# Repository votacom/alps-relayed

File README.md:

# alps-relayed
Input selection circuit board replacing the Alps ASD-1025 and ASD-1017 motor switches (and possibly others) in Pioneer's A-50xR, A-550R and A-450R amplifiers (and possibly others), using fast relays. The switching circuit supports the amplifier's native remote control and is faster than the motor switch (typically 42 milliseconds on average).

## Supported amplifiers
This circuit board is designed to replace ASD-1025 in the Pioneer A-502R, A-502R-G, A-503R, and A-503R-G amplifier models. It can also replace ASD-1017 in the Pioneer A-501R, A-550R and A-450R models, though with the downside of the "Source" recording input selection not working anymore (unless four jumpers are added, but then tape looping becomes possible, which is inhibited by ASD-1017). Since the ASD-1025 was also used in A-602R, it may be possible to use it in this model as well, but this has not been verified.

## Versions
There are two versions of the replacement board: v1 and v2.
v1 is larger, connects to the motor pin holes via individual connectors, and includes a direct plug connector to the motor driver IC pin holes and an additional stabilizing blind plug connector. Its layout is only applicable to the A-502R and A-503R models.
v2 is more compact, uses only three broad connectors to the motor pin holes, and does not directly plug into the motor driver IC pin holes, but uses a patch wire connector instead. This way, it can also be used in the A-501R, A-550R and A-450R models.
The two versions also slightly differ in their circuitry.

## Installation in Pioneer A-502R / A-503R

### v1 Installation
To install the v1 replacement board,
1. uninstall (unsolder) from the amplifier's input assembly board
   - the switch motor,
   - the motor driver IC (TA7291S), and
   - the nearby tall electrolytic capacitor (labelled C293),
2. solder simple vertical pin headers (e.g. Samtek TSW-1xx) into the input assembly board as follows:
   - a single-row 9-pin header strip where the motor driver IC was,
   - a single pin in each of the now-free motor's drill holes that would be connected by the replacement board (20 in total), and
   - a single pin in the free drill hole that would be connected by the replacement board's single corner socket, right next to the ribbon cable socket,
3. plug the replacement board on the input assembly board, aligning the selection board's new pins with the replacement board's sockets.

### v2 Installation
To install the v2 replacement board,
1. uninstall (unsolder) from the amplifier's input assembly board
   - the switch motor, and
   - the motor driver IC (TA7291S),
2. solder a single-row 9-pin header strip (e.g. Samtek TSW-1xx) to replace the motor driver IC,
3. from three Hirose DF3A-12P-2DSA pin headers, clip off every other pin (the odd-numbered pins) and solder them into the upper rows of the three double-row motor drill holes (pay attention to orientation),
4. stick a plain pin (min. 7mm) in each of the replacement board's two "Selection" sockets,
5. plug the replacement board on the input assembly board (the two plain pins extending from the replacement board should go through pin holes the on input assembly board),
6. use four individual jumper wires to connect the replacement board's +5V, GND, ↑, and ↓ pins to four of the motor driver IC's replacement header strip's pins (counted from left to right, starting at 1) as follows:
   - +5V connects to pin number 4,
   - GND connects to pin number 5,
   - ↑ and ↓ connect to pins number 1 and 9 in any order.

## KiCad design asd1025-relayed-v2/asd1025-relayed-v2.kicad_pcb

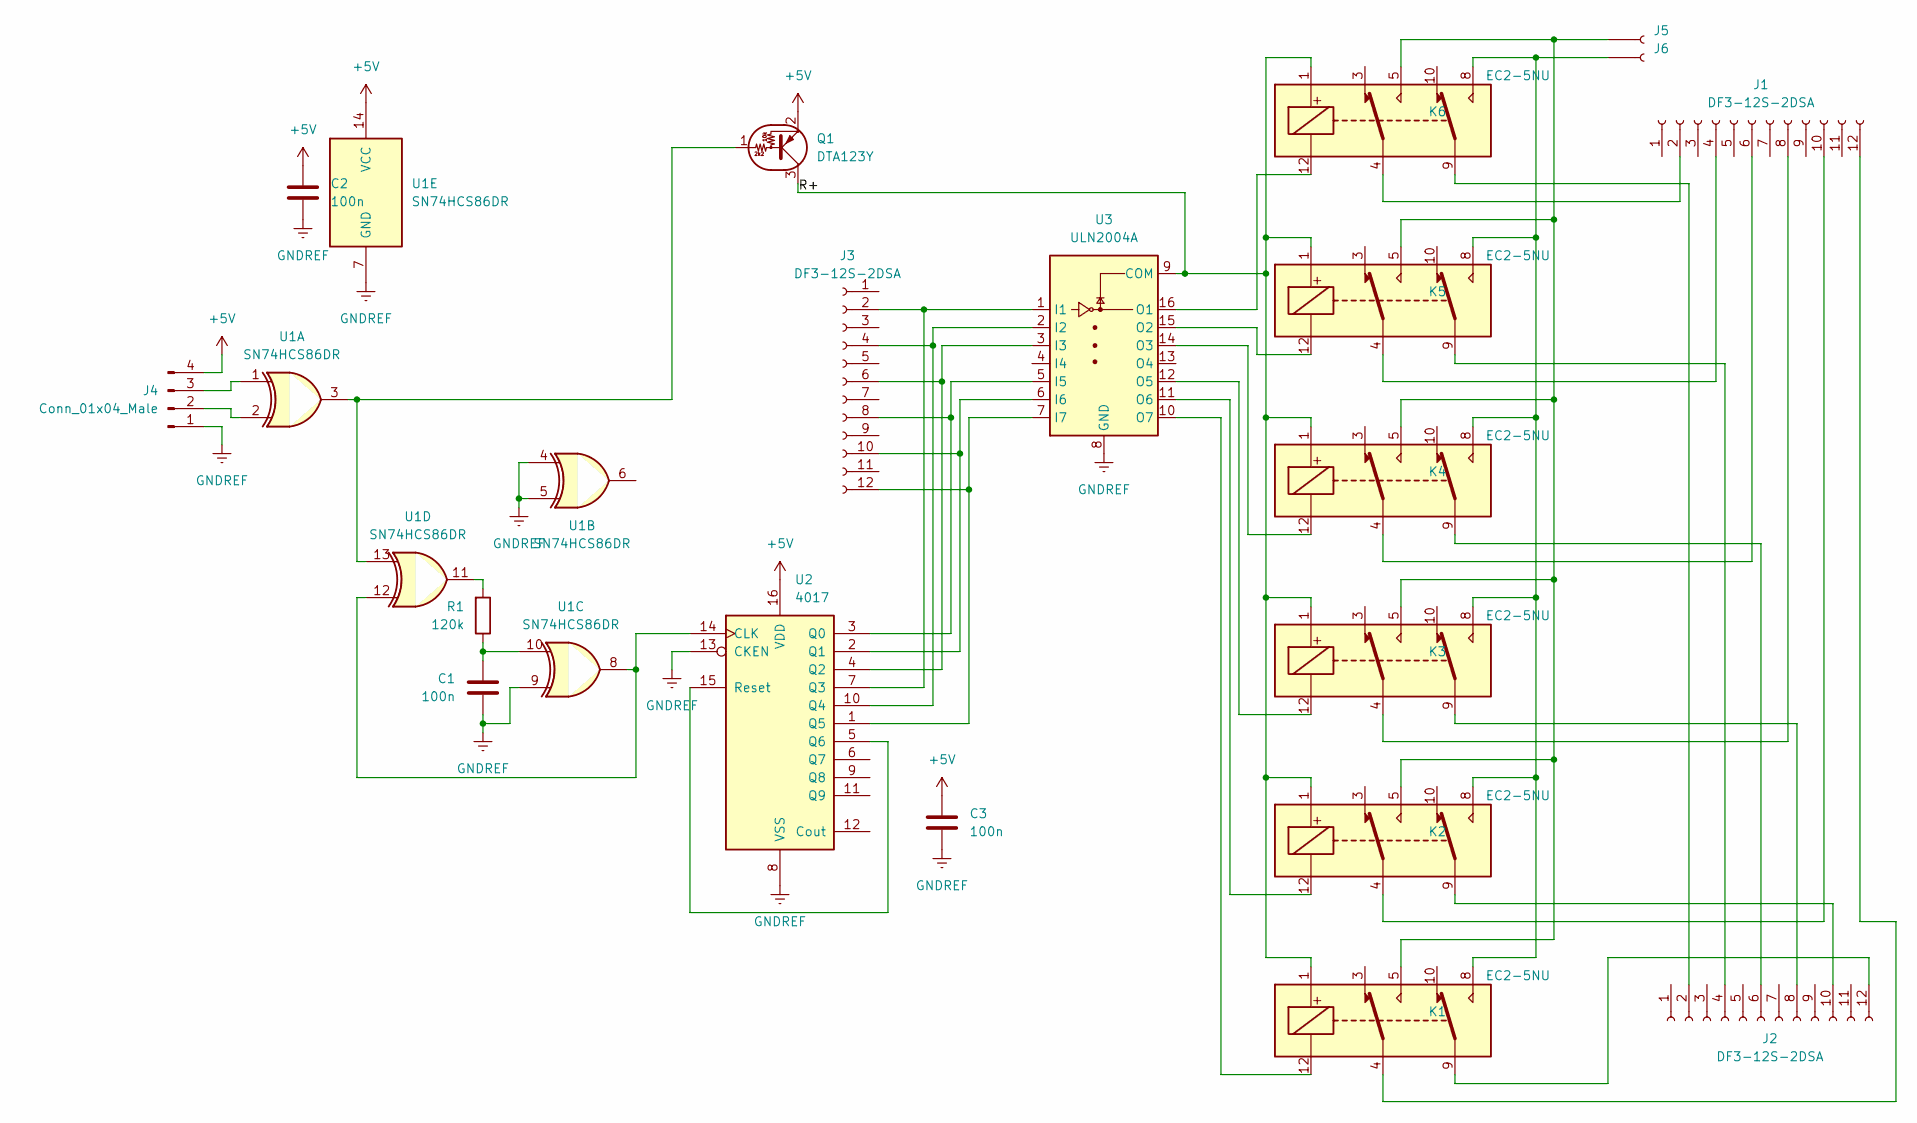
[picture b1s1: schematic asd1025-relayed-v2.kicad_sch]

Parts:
C1, C3: 100n; C_Disc_D5.1mm_W3.2mm_P5.00mm
C2: 100n; C_0402_1005Metric_Pad0.74x0.62mm_HandSolder
J1, J2, J3: DF3-12S-2DSA; Hirose_DF3-12S-2DSA_1x12_P2.00mm_Vertical
J4: Conn_01x04_Male; PinHeader_1x04_P2.54mm_Horizontal
J5, J6: Conn_01x01_Female; PinSocket_1x01_P2.54mm_Vertical
K1, K2, K3, K4, K5, K6: EC2-5NU; Relay_DPDT_Kemet_EC2
Q1: DTA123Y; SOT-23
R1: 120k; R_Axial_DIN0207_L6.3mm_D2.5mm_P10.16mm_Horizontal
U1: SN74HCS86DR; SOIC-14_3.9x8.7mm_P1.27mm
U2: 4017; SOIC-16_3.9x9.9mm_P1.27mm
U3: ULN2004A; DIP-16_W7.62mm

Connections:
+5V: C2.1, C3.1, J4.4, Q1.2 (E), U1.14 (VCC), U2.16 (VDD)
/R+: K1.1, K2.1, K3.1, K4.1, K5.1, K6.1, Q1.3 (C), U3.9 (COM)
GNDREF: C1.1, C2.2, C3.2, J4.1, U1.4, U1.5, U1.7 (GND), U1.9, U2.8 (VSS), U2.13 (CKEN), U3.8 (GND)
unnamed: C1.2, R1.1, U1.10
unnamed: J1.2, K6.4
unnamed: J1.4, K5.4
unnamed: J1.6, K4.4
unnamed: J1.8, K3.4
unnamed: J1.10, K2.4
unnamed: J1.12, K1.4
unnamed: J2.2, K6.9
unnamed: J2.4, K5.9
unnamed: J2.6, K4.9
unnamed: J2.8, K3.9
unnamed: J2.10, K2.9
unnamed: J2.12, K1.9
unnamed: J3.2, U2.7 (Q3), U3.1 (I1)
unnamed: J3.4, U2.10 (Q4), U3.2 (I2)
unnamed: J3.6, U2.4 (Q2), U3.3 (I3)
unnamed: J3.8, U2.3 (Q0), U3.5 (I5)
unnamed: J3.10, U2.2 (Q1), U3.6 (I6)
unnamed: J3.12, U2.1 (Q5), U3.7 (I7)
unnamed: J4.2, U1.2
unnamed: J4.3, U1.1
unnamed: J5.1, K1.5, K2.5, K3.5, K4.5, K5.5, K6.5
unnamed: J6.1, K1.8, K2.8, K3.8, K4.8, K5.8, K6.8
unnamed: K1.12, U3.10 (O7)
unnamed: K2.12, U3.11 (O6)
unnamed: K3.12, U3.12 (O5)
unnamed: K4.12, U3.14 (O3)
unnamed: K5.12, U3.15 (O2)
unnamed: K6.12, U3.16 (O1)
unnamed: R1.2, U1.11
unnamed: Q1.1 (B), U1.3, U1.13
unnamed: U1.8, U1.12, U2.14 (CLK)
unnamed: U2.5 (Q6), U2.15 (Reset)

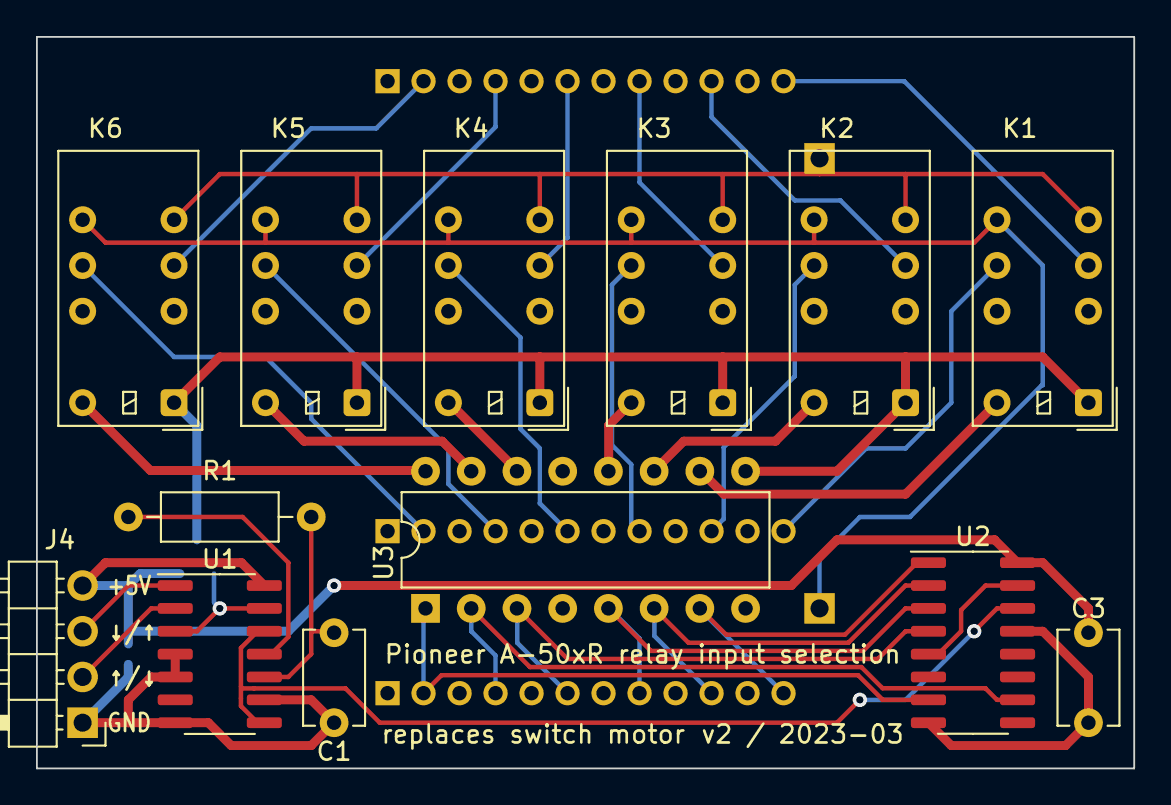
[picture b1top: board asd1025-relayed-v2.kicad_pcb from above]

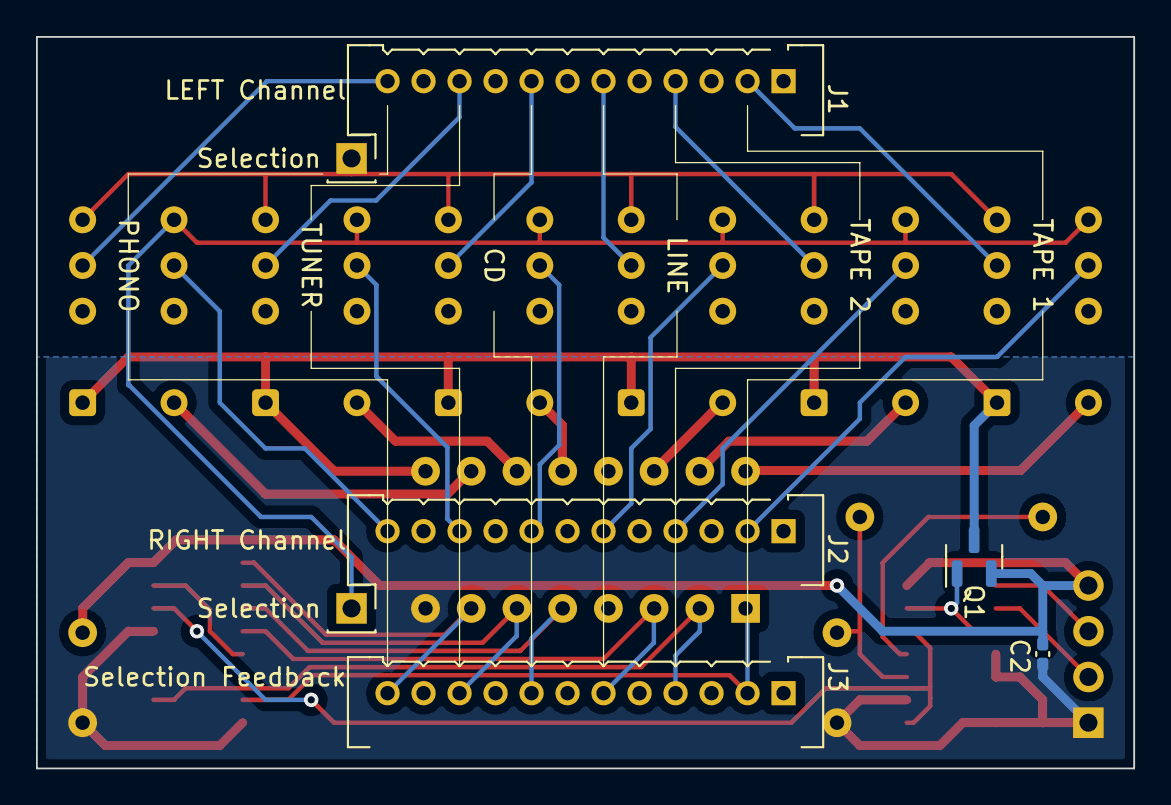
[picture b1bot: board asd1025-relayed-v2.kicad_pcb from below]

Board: 2 copper layers, 61.0 x 40.6 mm, 20 parts (7 on the bottom side), 36 nets.

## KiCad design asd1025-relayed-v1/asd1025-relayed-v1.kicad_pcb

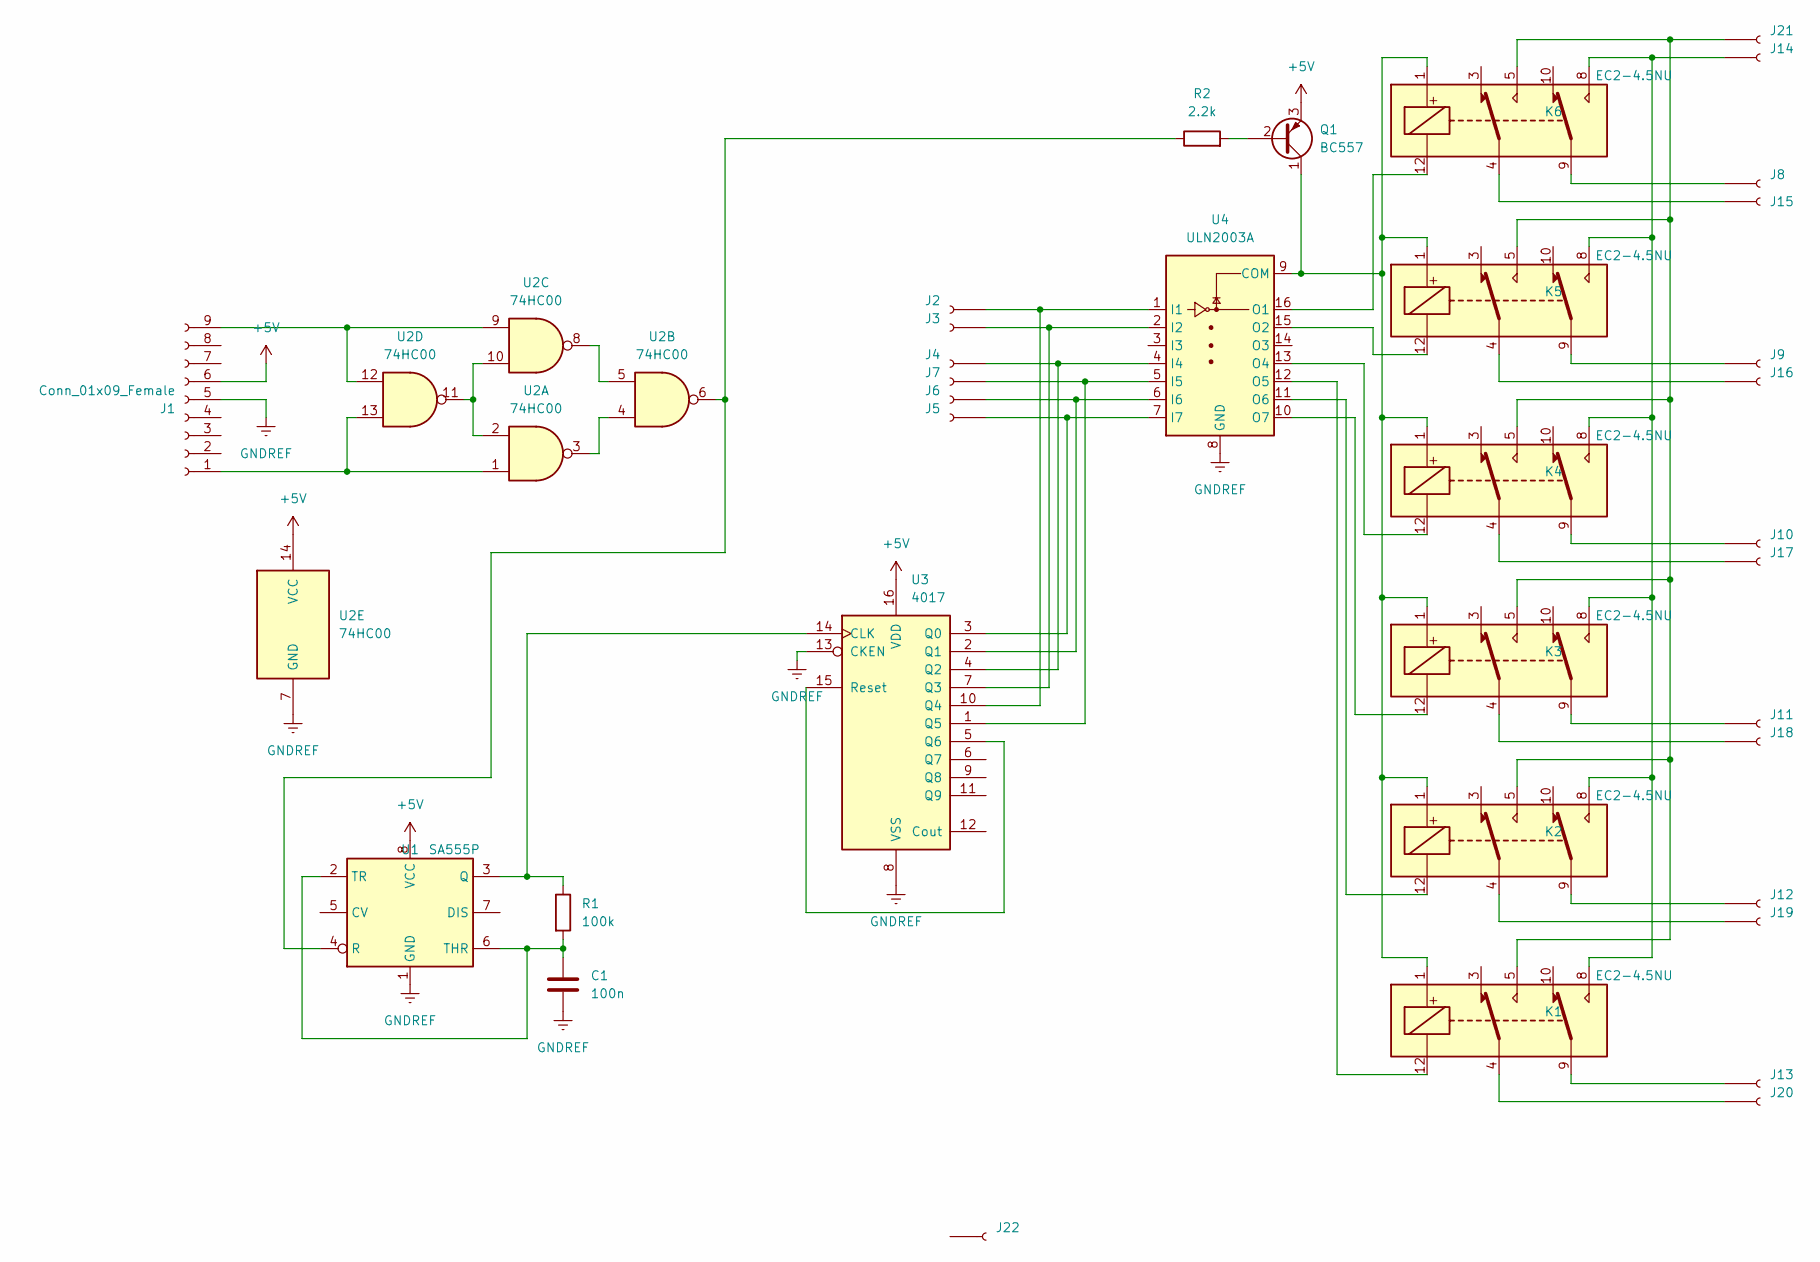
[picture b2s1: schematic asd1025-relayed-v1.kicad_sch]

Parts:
C1: 100n; C_Disc_D5.1mm_W3.2mm_P5.00mm
J1: Conn_01x09_Female; PinSocket_1x09_P2.54mm_Vertical
J2, J3, J4, J5, J6, J7, J8, J9, J10, J11, J12, J13, J14, J15, J16, J17, J18, J19, J20, J21, J22: Conn_01x01_Female; PinSocket_1x01_P2.54mm_Vertical
K1, K2, K3, K4, K5, K6: EC2-4.5NU; Relay_DPDT_Kemet_EC2
Q1: BC557; TO-92_Inline_Wide
R1: 100k; R_Axial_DIN0207_L6.3mm_D2.5mm_P10.16mm_Horizontal
R2: 2.2k; R_Axial_DIN0207_L6.3mm_D2.5mm_P10.16mm_Horizontal
U1: SA555P; DIP-8_W7.62mm
U2: 74HC00; DIP-14_W7.62mm
U3: 4017; DIP-16_W7.62mm
U4: ULN2003A; DIP-16_W7.62mm

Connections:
+5V: J1.6, Q1.3 (E), U1.8 (VCC), U2.14 (VCC), U3.16 (VDD)
GNDREF: C1.2, J1.5, U1.1 (GND), U2.7 (GND), U3.8 (VSS), U3.13 (CKEN), U4.8 (GND)
unnamed: C1.1, R1.2, U1.2 (TR), U1.6 (THR)
unnamed: J1.1, U2.1, U2.13
unnamed: J2.1, U3.10 (Q4), U4.1 (I1)
unnamed: J3.1, U3.7 (Q3), U4.2 (I2)
unnamed: J4.1, U3.4 (Q2), U4.4 (I4)
unnamed: J5.1, U3.3 (Q0), U4.7 (I7)
unnamed: J6.1, U3.2 (Q1), U4.6 (I6)
unnamed: J7.1, U3.1 (Q5), U4.5 (I5)
unnamed: J8.1, K6.9
unnamed: J9.1, K5.9
unnamed: J10.1, K4.9
unnamed: J11.1, K3.9
unnamed: J12.1, K2.9
unnamed: J13.1, K1.9
unnamed: J14.1, K1.8, K2.8, K3.8, K4.8, K5.8, K6.8
unnamed: J15.1, K6.4
unnamed: J16.1, K5.4
unnamed: J17.1, K4.4
unnamed: J18.1, K3.4
unnamed: J19.1, K2.4
unnamed: J20.1, K1.4
unnamed: J21.1, K1.5, K2.5, K3.5, K4.5, K5.5, K6.5
unnamed: K1.1, K2.1, K3.1, K4.1, K5.1, K6.1, Q1.1 (C), U4.9 (COM)
unnamed: K1.12, U4.12 (O5)
unnamed: K2.12, U4.11 (O6)
unnamed: K3.12, U4.10 (O7)
unnamed: K4.12, U4.13 (O4)
unnamed: K5.12, U4.15 (O2)
unnamed: K6.12, U4.16 (O1)
unnamed: Q1.2 (B), R2.2
unnamed: R1.1, U1.3 (Q), U3.14 (CLK)
unnamed: R2.1, U1.4 (R), U2.6
unnamed: U2.3, U2.4
unnamed: U2.5, U2.8
unnamed: J1.9, U2.9, U2.12
unnamed: U2.2, U2.10, U2.11
unnamed: U3.5 (Q6), U3.15 (Reset)

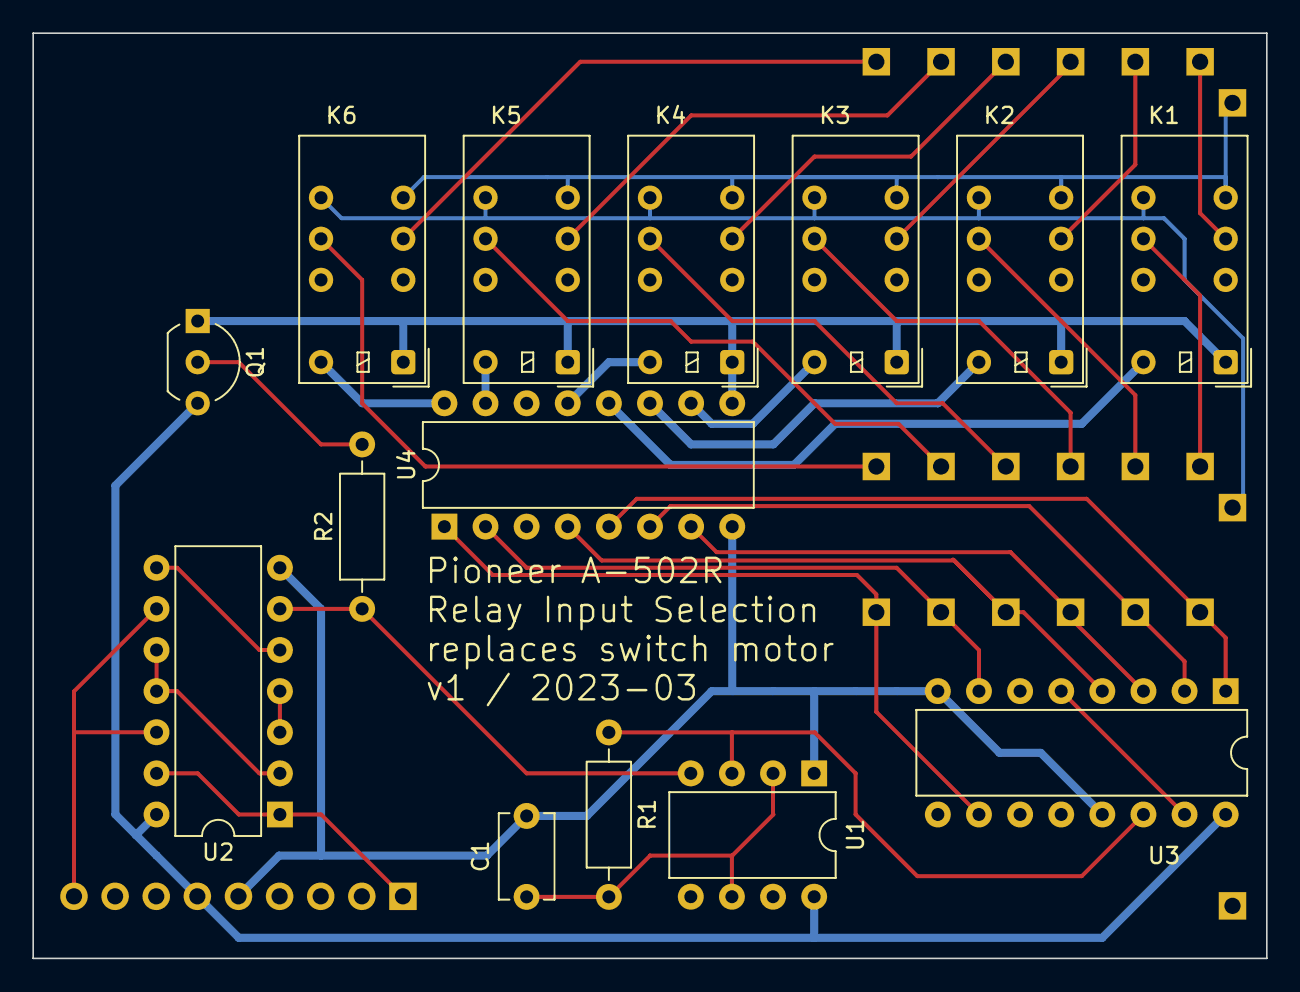
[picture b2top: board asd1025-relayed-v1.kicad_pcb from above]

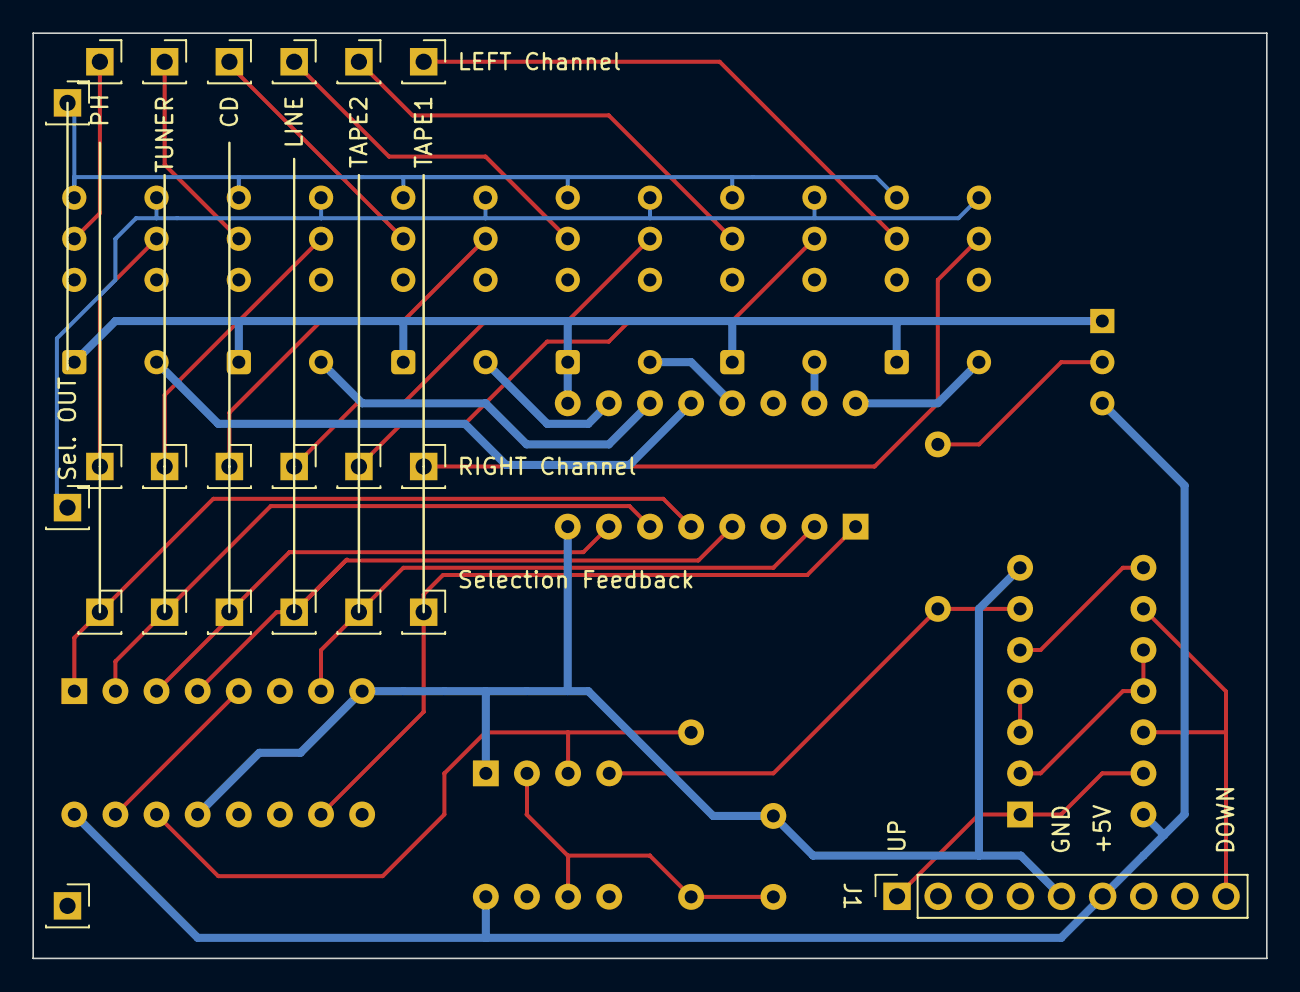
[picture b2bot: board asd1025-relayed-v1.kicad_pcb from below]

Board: 2 copper layers, 76.2 x 57.2 mm, 36 parts (22 on the bottom side), 39 nets.

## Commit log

2023-02-23 Update README.md
    add supported amplifiers section
2023-02-23 Initial population of the repository with KiCad files
2023-02-23 Update README.md
    update supported amplifiers
2023-02-23 add 3D rendering picture
2023-02-23 Update README.md
    add 3D rendering in README
2023-02-23 add 3D rendering picture of the bottom of the board
2023-02-23 Update README.md
    add bottom 3D rendering image to readme
2023-02-23 Update README.md
    clarify pioneer part numbers
2023-02-23 Update README.md
    add installation guide
2023-02-25 add v2 design
2023-02-25 remove duplicate files
2023-02-25 rename first project to -v1
2023-02-25 Update README.md
    add v2 to readme
2023-02-26 Update README.md
    clarify remote control support and speed
2023-02-26 fix mistake in v2 board about oscillator timing logic, nicer bottom silkscreen, no clock enabled signal needed anymore
2023-02-26 fix readme links to renderings
2023-02-27 change oscillator frequency to minimum to ensure 10ms between relai cut-off and on-switching
2023-02-27 Update README.md
    Generalize README to support possible other ALPS motors and amps.
2023-03-01 Update README.md
    add support for A-501R, A-550R, A-450R
2023-03-05 fix v1: relays would switch by passing current through base-emittor-resistors in darlington array even if main transistor Q1 is off
2023-03-05 fix v2: relays would switch by passing current through base-emittor-resistors in darlington array even if main transistor Q1 is off
